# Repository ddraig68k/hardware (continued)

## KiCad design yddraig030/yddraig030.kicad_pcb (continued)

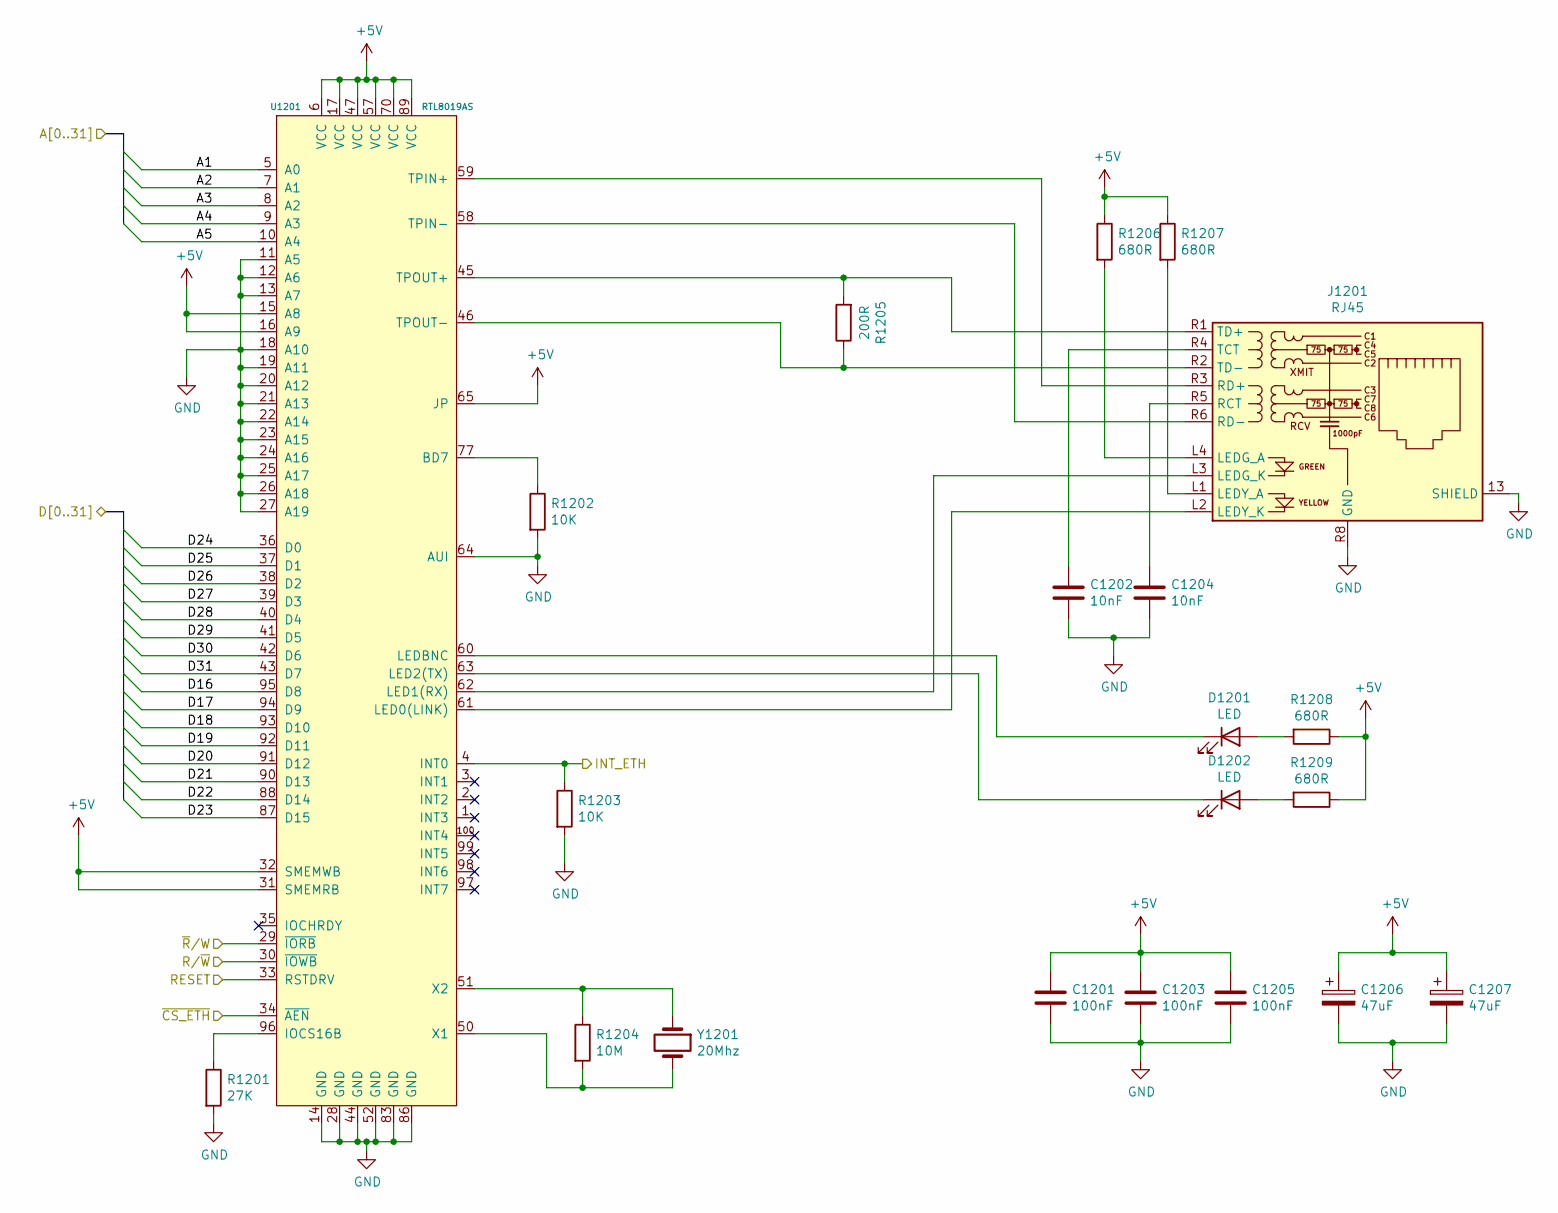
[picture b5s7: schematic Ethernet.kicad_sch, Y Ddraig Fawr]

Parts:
C1201, C1203, C1205: 100nF; C_0805_2012Metric
C1202, C1204: 10nF; C_0805_2012Metric
C1206, C1207: 47uF; CP_Elec_4x5.7
D1201, D1202: LED; LED_1206_3216Metric
J1201: RJ45; RJ45_Amphenol_RJMG1BD3B8K1ANR
R1201: 27K; R_0805_2012Metric
R1202, R1203: 10K; R_0805_2012Metric
R1204: 10M; R_0805_2012Metric
R1205: 200R; R_0805_2012Metric
R1206, R1207, R1208, R1209: 680R; R_0805_2012Metric
U1201: RTL8019AS
Y1201: 20Mhz; Crystal_SMD_HC49-SD

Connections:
+5V: C1201.1, C1203.1, C1205.1, C1206.1, C1207.1, R1206.1, R1207.1, R1208.1, R1209.1, U1201.6 (VCC), U1201.15 (A8), U1201.16 (A9), U1201.17 (VCC), U1201.31 (SMEMRB), U1201.32 (SMEMWB), U1201.47 (VCC), U1201.57 (VCC), U1201.65 (JP), U1201.70 (VCC), U1201.89 (VCC); also elsewhere on the board
/CPU and FPU/R/~W: U1201.30 (~IOWB); also elsewhere on the board
/Decode and Logic/INT_ETH: R1203.1, U1201.4 (INT0); also elsewhere on the board
/Decode and Logic/RESET: U1201.33 (RSTDRV); also elsewhere on the board
/Decode and Logic/~CS_ETH: U1201.34 (~AEN); also elsewhere on the board
/Decode and Logic/~R/W: U1201.29 (~IORB); also elsewhere on the board
/Ethernet/D16: U1201.95 (D8)
/Ethernet/D17: U1201.94 (D9)
/Ethernet/D18: U1201.93 (D10)
/Ethernet/D19: U1201.92 (D11)
/Ethernet/D20: U1201.91 (D12)
/Ethernet/D21: U1201.90 (D13)
/Ethernet/D22: U1201.88 (D14)
/Ethernet/D23: U1201.87 (D15)
/Ethernet/D24: U1201.36 (D0)
/Ethernet/D25: U1201.37 (D1)
/Ethernet/D26: U1201.38 (D2)
/Ethernet/D27: U1201.39 (D3)
/Ethernet/D28: U1201.40 (D4)
/Ethernet/D29: U1201.41 (D5)
/Ethernet/D30: U1201.42 (D6)
/Ethernet/D31: U1201.43 (D7)
/ROM and SRAM/A1: U1201.5 (A0); also elsewhere on the board
/ROM and SRAM/A2: U1201.7 (A1); also elsewhere on the board
/ROM and SRAM/A3: U1201.8 (A2); also elsewhere on the board
/ROM and SRAM/A4: U1201.9 (A3); also elsewhere on the board
/ROM and SRAM/A5: U1201.10 (A4); also elsewhere on the board
unnamed: C1202.1, J1201.R4 (TCT)
unnamed: C1204.1, J1201.R5 (RCT)
unnamed: D1201.1 (K), U1201.60 (LEDBNC)
unnamed: D1201.2 (A), R1208.2
unnamed: D1202.1 (K), U1201.63 (LED2(TX))
unnamed: D1202.2 (A), R1209.2
unnamed: J1201.L1 (LEDY_A), R1207.2
unnamed: J1201.L2 (LEDY_K), U1201.61 (LED0(LINK))
unnamed: J1201.L3 (LEDG_K), U1201.62 (LED1(RX))
unnamed: J1201.L4 (LEDG_A), R1206.2
unnamed: J1201.R1 (TD+), R1205.2, U1201.45 (TPOUT+)
unnamed: J1201.R2 (TD-), R1205.1, U1201.46 (TPOUT-)
unnamed: J1201.R3 (RD+), U1201.59 (TPIN+)
unnamed: J1201.R6 (RD-), U1201.58 (TPIN-)
unnamed: R1201.1, U1201.96 (IOCS16B)
unnamed: R1202.1, U1201.77 (BD7)
unnamed: R1204.1, U1201.51 (X2), Y1201.1
unnamed: R1204.2, U1201.50 (X1), Y1201.2

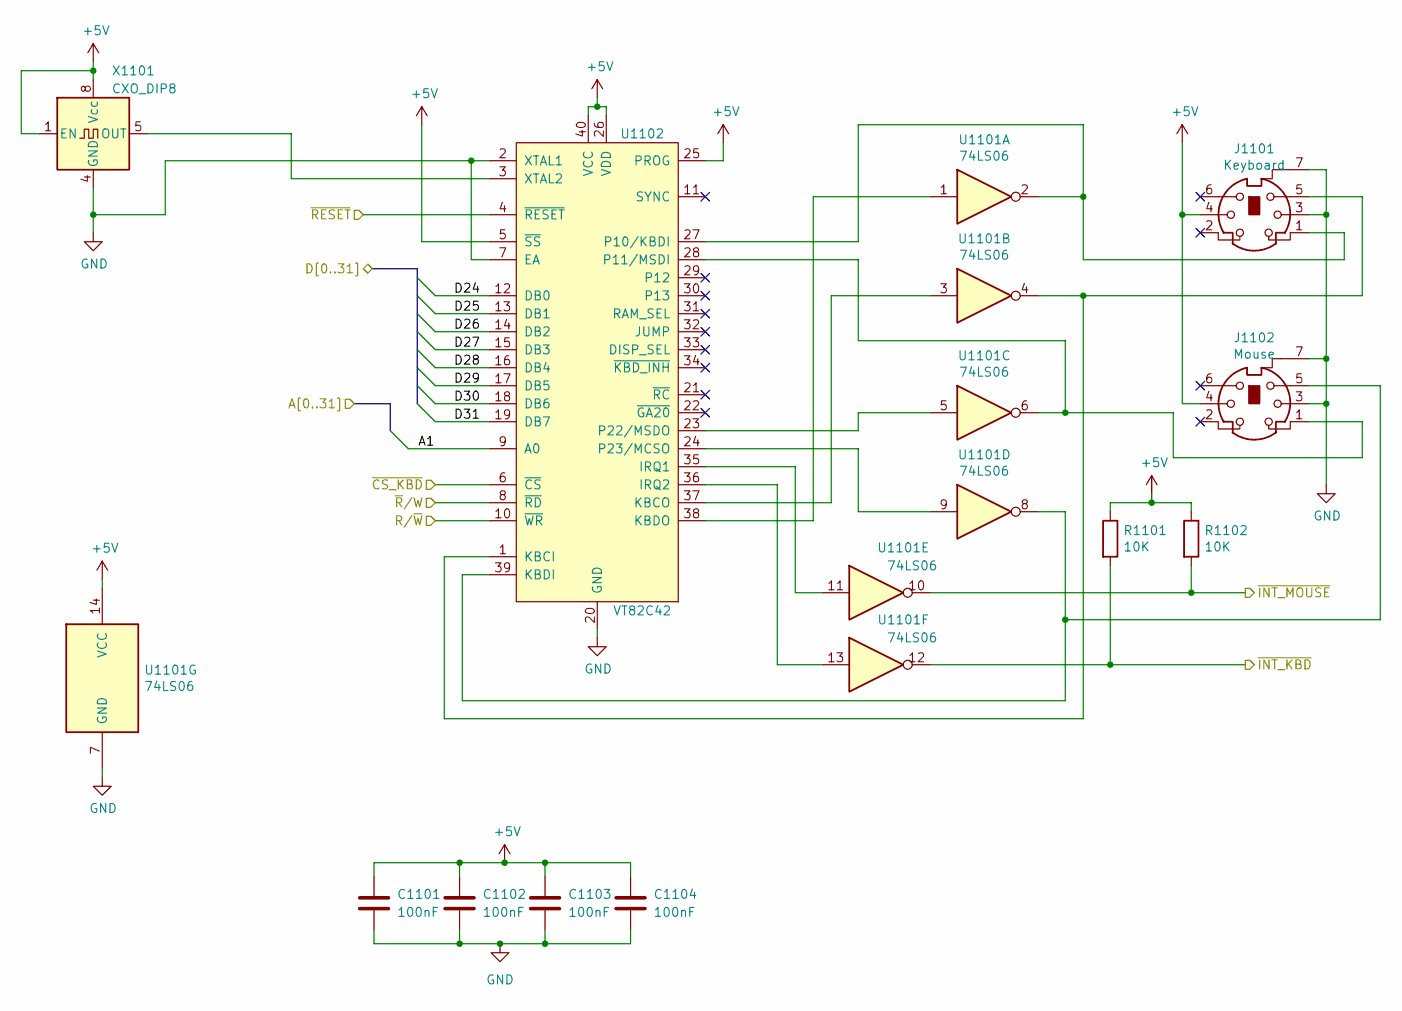
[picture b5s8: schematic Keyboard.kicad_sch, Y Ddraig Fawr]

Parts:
C1101, C1102, C1103, C1104: 100nF; C_Disc_D3.8mm_W2.6mm_P2.50mm
J1101: Keyboard; MINI-DIN-6-FULL-SHIELD
J1102: Mouse; MINI-DIN-6-FULL-SHIELD
R1101, R1102: 10K; R_Axial_DIN0207_L6.3mm_D2.5mm_P10.16mm_Horizontal
U1101: 74LS06; DIP-14_W7.62mm_Socket
U1102: VT82C42; DIP-40_W15.24mm_Socket
X1101: CXO_DIP8; Oscillator_DIP-8

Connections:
+5V: C1101.1, C1102.1, C1103.1, C1104.1, J1101.4, J1102.4, R1101.1, R1102.1, U1101.14 (VCC), U1102.5 (~SS), U1102.25 (PROG), U1102.26 (VDD), U1102.40 (VCC), X1101.1 (EN), X1101.8 (Vcc); also elsewhere on the board
/CPU and FPU/R/~W: U1102.10 (~WR); also elsewhere on the board
/CPU and FPU/~RESET: U1102.4 (~RESET); also elsewhere on the board
/Decode and Logic/~CS_KBD: U1102.6 (~CS); also elsewhere on the board
/Decode and Logic/~R/W: U1102.8 (~RD); also elsewhere on the board
/Interrupts/~INT_KBD: R1101.2, U1101.12; also elsewhere on the board
/Interrupts/~INT_MOUSE: R1102.2, U1101.10; also elsewhere on the board
/ROM and SRAM/A1: U1102.9 (A0); also elsewhere on the board
/ROM and SRAM/D24: U1102.12 (DB0); also elsewhere on the board
/ROM and SRAM/D25: U1102.13 (DB1); also elsewhere on the board
/ROM and SRAM/D26: U1102.14 (DB2); also elsewhere on the board
/ROM and SRAM/D27: U1102.15 (DB3); also elsewhere on the board
/ROM and SRAM/D28: U1102.16 (DB4); also elsewhere on the board
/ROM and SRAM/D29: U1102.17 (DB5); also elsewhere on the board
/ROM and SRAM/D30: U1102.18 (DB6); also elsewhere on the board
/ROM and SRAM/D31: U1102.19 (DB7); also elsewhere on the board
unnamed: J1101.1, U1101.2, U1102.27 (P10/KBDI)
unnamed: J1101.5, U1101.4, U1102.1 (KBCI)
unnamed: J1102.1, U1101.6, U1102.28 (P11/MSDI)
unnamed: J1102.5, U1101.8, U1102.39 (KBDI)
unnamed: U1101.1, U1102.38 (KBDO)
unnamed: U1101.3, U1102.37 (KBCO)
unnamed: U1101.5, U1102.23 (P22/MSDO)
unnamed: U1101.9, U1102.24 (P23/MCSO)
unnamed: U1101.11, U1102.35 (IRQ1)
unnamed: U1101.13, U1102.36 (IRQ2)
unnamed: U1102.3 (XTAL2), X1101.5 (OUT)

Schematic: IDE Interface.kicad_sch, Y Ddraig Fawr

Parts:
C601, C602, C603, C604: 100nF; C_0805_2012Metric
D601: Blue; LED_1206_3216Metric
J601: IDE LED; PinHeader_1x02_P2.54mm_Vertical
J602: IDE 5V; PinHeader_1x02_P2.54mm_Vertical
J603: IDE_Interface; IDC-Header_2x20_P2.54mm_Vertical
Q601: 2N7000; TO-92_Inline
R601, R602: 330R; R_0805_2012Metric
R603: 1M; R_0805_2012Metric
R604, R605: 10K; R_0805_2012Metric
RN601, RN602: 22R; R_Array_SIP8
U601: 74LS139; SO-16_3.9x9.9mm_P1.27mm

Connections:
+5V: C601.1, C602.1, C603.1, C604.1, D601.2 (A), J601.2, J602.2, R603.1, R605.2, U601.13 (A1), U601.14 (A0), U601.15 (E), U601.16 (VCC); also elsewhere on the board
/CPU and FPU/R/~W: RN602.1 (R1.1); also elsewhere on the board
/CPU and FPU/~RESET: RN602.5 (R3.1); also elsewhere on the board
/Decode and Logic/~CS_IDE: U601.1 (E); also elsewhere on the board
/Decode and Logic/~R/W: RN602.3 (R2.1); also elsewhere on the board
/IDE/ACTIVE: J603.39 (~ACTIVE), R601.2, R602.2
/IDE/~INT_IDE: Q601.3 (D), R603.2; also elsewhere on the board
/ROM and SRAM/A1: RN601.1 (R1.1); also elsewhere on the board
/ROM and SRAM/A2: RN601.3 (R2.1); also elsewhere on the board
/ROM and SRAM/A3: RN601.5 (R3.1); also elsewhere on the board
/ROM and SRAM/A7: U601.2 (A0); also elsewhere on the board
/ROM and SRAM/D16: J603.4 (D8); also elsewhere on the board
/ROM and SRAM/D17: J603.6 (D9); also elsewhere on the board
/ROM and SRAM/D18: J603.8 (D10); also elsewhere on the board
/ROM and SRAM/D19: J603.10 (D11); also elsewhere on the board
/ROM and SRAM/D20: J603.12 (D12); also elsewhere on the board
/ROM and SRAM/D21: J603.14 (D13); also elsewhere on the board
/ROM and SRAM/D22: J603.16 (D14); also elsewhere on the board
/ROM and SRAM/D23: J603.18 (D15); also elsewhere on the board
/ROM and SRAM/D24: J603.17 (D0); also elsewhere on the board
/ROM and SRAM/D25: J603.15 (D1); also elsewhere on the board
/ROM and SRAM/D26: J603.13 (D2); also elsewhere on the board
/ROM and SRAM/D27: J603.11 (D3); also elsewhere on the board
/ROM and SRAM/D28: J603.9 (D4); also elsewhere on the board
/ROM and SRAM/D29: J603.7 (D5); also elsewhere on the board
/ROM and SRAM/D30: J603.5 (D6); also elsewhere on the board
/ROM and SRAM/D31: J603.3 (D7); also elsewhere on the board
unnamed: D601.1 (K), R602.1
unnamed: J601.1, R601.1
unnamed: J602.1, J603.20 (KEY)
unnamed: J603.1 (~RESET), RN602.6 (R3.2)
unnamed: J603.21 (DMARQ), R604.1
unnamed: J603.23 (~DIOW), RN602.2 (R1.2)
unnamed: J603.25 (~DIOR), RN602.4 (R2.2)
unnamed: J603.29 (~DMACK), R605.1
unnamed: J603.33 (A1), RN601.4 (R2.2)
unnamed: J603.35 (A0), RN601.2 (R1.2)
unnamed: J603.36 (A2), RN601.6 (R3.2)
unnamed: J603.37 (~IDE_CS0), U601.4 (O0)
unnamed: J603.38 (~IDE_CS1), U601.5 (O1)

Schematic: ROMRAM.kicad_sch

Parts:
C401, C402, C403, C404, C405: 100nF; C_0805_2012Metric
U401, U403: SST39SF040; DIP-32_W15.24mm_Socket
U402, U404: AS6C4008-55PCN; DIP-32_W15.24mm
U405: 74LS32; SO-14_3.9x8.65mm_P1.27mm

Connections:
+5V: C401.1, C402.1, C403.1, C404.1, C405.1, U401.32 (VCC), U402.32 (VCC), U403.32 (VCC), U404.32 (VCC), U405.14 (VCC); also elsewhere on the board
/CPU and FPU/R/~W: U401.31 (PGM), U402.29 (WE#), U403.31 (PGM), U404.29 (WE#); also elsewhere on the board
/Decode and Logic/~CS_ROM: U405.2, U405.10; also elsewhere on the board
/Decode and Logic/~CS_SRAM: U405.5, U405.13; also elsewhere on the board
/Decode and Logic/~LDS: U405.9, U405.12; also elsewhere on the board
/Decode and Logic/~R/W: U401.24 (OE), U402.24 (OE#), U403.24 (OE), U404.24 (OE#); also elsewhere on the board
/Decode and Logic/~UDS: U405.1, U405.4; also elsewhere on the board
/ROM and SRAM/A1: U401.12 (A0), U402.12 (A0), U403.12 (A0), U404.12 (A0); also elsewhere on the board
/ROM and SRAM/A2: U401.11 (A1), U402.11 (A1), U403.11 (A1), U404.11 (A1); also elsewhere on the board
/ROM and SRAM/A3: U401.10 (A2), U402.10 (A2), U403.10 (A2), U404.10 (A2); also elsewhere on the board
/ROM and SRAM/A4: U401.9 (A3), U402.9 (A3), U403.9 (A3), U404.9 (A3); also elsewhere on the board
/ROM and SRAM/A5: U401.8 (A4), U402.8 (A4), U403.8 (A4), U404.8 (A4); also elsewhere on the board
/ROM and SRAM/A6: U401.7 (A5), U402.7 (A5), U403.7 (A5), U404.7 (A5); also elsewhere on the board
/ROM and SRAM/A7: U401.6 (A6), U402.6 (A6), U403.6 (A6), U404.6 (A6); also elsewhere on the board
/ROM and SRAM/A8: U401.5 (A7), U402.5 (A7), U403.5 (A7), U404.5 (A7); also elsewhere on the board
/ROM and SRAM/A9: U401.27 (A8), U402.27 (A8), U403.27 (A8), U404.27 (A8); also elsewhere on the board
/ROM and SRAM/A10: U401.26 (A9), U402.26 (A9), U403.26 (A9), U404.26 (A9); also elsewhere on the board
/ROM and SRAM/A11: U401.23 (A10), U402.23 (A10), U403.23 (A10), U404.23 (A10); also elsewhere on the board
/ROM and SRAM/A12: U401.25 (A11), U402.25 (A11), U403.25 (A11), U404.25 (A11); also elsewhere on the board
/ROM and SRAM/A13: U401.4 (A12), U402.4 (A12), U403.4 (A12), U404.4 (A12); also elsewhere on the board
/ROM and SRAM/A14: U401.28 (A13), U402.28 (A13), U403.28 (A13), U404.28 (A13); also elsewhere on the board
/ROM and SRAM/A15: U401.29 (A14), U402.3 (A14), U403.29 (A14), U404.3 (A14); also elsewhere on the board
/ROM and SRAM/A16: U401.3 (A15), U402.31 (A15), U403.3 (A15), U404.31 (A15); also elsewhere on the board
/ROM and SRAM/A17: U401.2 (A16), U402.2 (A16), U403.2 (A16), U404.2 (A16); also elsewhere on the board
/ROM and SRAM/A18: U401.30 (A17), U402.30 (A17), U403.30 (A17), U404.30 (A17); also elsewhere on the board
/ROM and SRAM/A19: U401.1 (A18), U402.1 (A18), U403.1 (A18), U404.1 (A18); also elsewhere on the board
/ROM and SRAM/D16: U401.13 (D0), U402.13 (DQ0); also elsewhere on the board
/ROM and SRAM/D17: U401.14 (D1), U402.14 (DQ1); also elsewhere on the board
/ROM and SRAM/D18: U401.15 (D2), U402.15 (DQ2); also elsewhere on the board
/ROM and SRAM/D19: U401.17 (D3), U402.17 (DQ3); also elsewhere on the board
/ROM and SRAM/D20: U401.18 (D4), U402.18 (DQ4); also elsewhere on the board
/ROM and SRAM/D21: U401.19 (D5), U402.19 (DQ5); also elsewhere on the board
/ROM and SRAM/D22: U401.20 (D6), U402.20 (DQ6); also elsewhere on the board
/ROM and SRAM/D23: U401.21 (D7), U402.21 (DQ7); also elsewhere on the board
/ROM and SRAM/D24: U403.13 (D0), U404.13 (DQ0); also elsewhere on the board
/ROM and SRAM/D25: U403.14 (D1), U404.14 (DQ1); also elsewhere on the board
/ROM and SRAM/D26: U403.15 (D2), U404.15 (DQ2); also elsewhere on the board
/ROM and SRAM/D27: U403.17 (D3), U404.17 (DQ3); also elsewhere on the board
/ROM and SRAM/D28: U403.18 (D4), U404.18 (DQ4); also elsewhere on the board
/ROM and SRAM/D29: U403.19 (D5), U404.19 (DQ5); also elsewhere on the board
/ROM and SRAM/D30: U403.20 (D6), U404.20 (DQ6); also elsewhere on the board
/ROM and SRAM/D31: U403.21 (D7), U404.21 (DQ7); also elsewhere on the board
unnamed: U401.22 (CE), U405.8
unnamed: U402.22 (CE#), U405.11
unnamed: U403.22 (CE), U405.3
unnamed: U404.22 (CE#), U405.6

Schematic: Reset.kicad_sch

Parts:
C201, C203: 10uF; CP_Elec_4x5.3
C202: 10nF; C_0805_2012Metric
D201: RED; LED_1206_3216Metric
D202: GREEN; LED_1206_3216Metric
J201: ExtReset; PinHeader_1x02_P2.54mm_Vertical
J202: Ext RUN LED; PinHeader_1x02_P2.54mm_Vertical
Q201, Q202: BC858; SOT-23
R201, R205: 1K; R_0805_2012Metric
R202, R206, R207: 150R; R_0805_2012Metric
R203: 10K; R_0805_2012Metric
R204: 38K; R_0805_2012Metric
SW201: Reset; SW_PUSH_6mm_H4.3mm
U201: NE555P; SO-8_5.3x6.2mm_P1.27mm

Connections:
+5V: Q201.2 (E), Q202.2 (E), R203.1, R204.1, U201.4 (R), U201.8 (VCC); also elsewhere on the board
/CPU and FPU/~RESET: R201.2; also elsewhere on the board
/Decode and Logic/RESET: U201.3 (Q); also elsewhere on the board
/Decode and Logic/RUN: R205.2; also elsewhere on the board
unnamed: C201.1, J201.1, R203.2, SW201.2 (B), U201.2 (TR)
unnamed: C202.1, U201.5 (CV)
unnamed: C203.1, R204.2, U201.6 (THR), U201.7 (DIS)
unnamed: D201.1 (K), R202.2
unnamed: D201.2 (A), Q201.3 (C)
unnamed: D202.1 (K), R206.2
unnamed: D202.2 (A), J202.1, Q202.3 (C)
unnamed: J202.2, R207.2
unnamed: Q201.1 (B), R201.1
unnamed: Q202.1 (B), R205.1

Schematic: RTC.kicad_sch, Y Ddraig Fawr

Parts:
BT1301: CR2032; BatteryHolder_Keystone_103_1x20mm
C1301, C1302: 100nF; C_0805_2012Metric
C1303: 10uF; CP_Elec_4x5.3
D1301: 1N4148; D_SOD-123
Q1301: BC549B; TO-92
Q1302: 2N4403; TO-92
R1301, R1302, R1303: 4K7; R_0805_2012Metric
U1301: RTC-72421; DIP-18_W7.62mm_Socket

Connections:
+5V: C1301.1, C1302.1, Q1302.1 (E), R1301.1; also elsewhere on the board
/CPU and FPU/R/~W: U1301.10 (~WR); also elsewhere on the board
/CPU and FPU/~RESET: U1301.15 (CS1); also elsewhere on the board
/Decode and Logic/~CS_RTC: U1301.2 (~CS0); also elsewhere on the board
/Decode and Logic/~R/W: U1301.8 (~RD); also elsewhere on the board
/ROM and SRAM/A1: U1301.4 (A0); also elsewhere on the board
/ROM and SRAM/A2: U1301.5 (A1); also elsewhere on the board
/ROM and SRAM/A3: U1301.6 (A2); also elsewhere on the board
/ROM and SRAM/A4: U1301.7 (A3); also elsewhere on the board
/ROM and SRAM/D24: U1301.14 (D0); also elsewhere on the board
/ROM and SRAM/D25: U1301.13 (D1); also elsewhere on the board
/ROM and SRAM/D26: U1301.12 (D2); also elsewhere on the board
/ROM and SRAM/D27: U1301.11 (D3); also elsewhere on the board
unnamed: BT1301.1 (+), D1301.2 (A)
unnamed: C1303.1, D1301.1 (K), Q1302.3 (C), U1301.3 (ALE), U1301.18 (VDD)
unnamed: Q1301.2 (B), R1301.2, R1302.1
unnamed: Q1301.3 (C), R1303.2
unnamed: Q1302.2 (B), R1303.1

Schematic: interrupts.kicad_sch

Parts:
C1501, C1502, C1503: 100nF; C_0805_2012Metric
RN1501, RN1502: 10K; R_Array_SIP9
U1501: 74LS541; SO-20_5.3x12.6mm_P1.27mm
U1502: 74LS21; SO-14_3.9x8.65mm_P1.27mm
U1503: 74LS148; SO-16_3.9x9.9mm_P1.27mm

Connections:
+5V: C1501.1, C1502.1, C1503.1, RN1501.1 (common), RN1502.1 (common), U1501.20 (VCC), U1502.14 (VCC), U1503.16 (VCC); also elsewhere on the board
/CPU and FPU/~IPL0: U1503.9 (S0); also elsewhere on the board
/CPU and FPU/~IPL1: U1503.7 (S1); also elsewhere on the board
/CPU and FPU/~IPL2: U1503.6 (S2); also elsewhere on the board
/Decode and Logic/~CS_INTERRUPT: U1501.1 (G1); also elsewhere on the board
/Decode and Logic/~INT_ETH: RN1502.6 (R5), U1503.3 (I6); also elsewhere on the board
/Expansion Slots/~EXT_IRQ1: RN1502.3 (R2), U1503.11 (I1); also elsewhere on the board
/Expansion Slots/~EXT_IRQ2: RN1501.8 (R7), U1501.3 (A1), U1502.2; also elsewhere on the board
/Expansion Slots/~EXT_IRQ3: RN1501.7 (R6), U1501.4 (A2), U1502.4; also elsewhere on the board
/Expansion Slots/~EXT_IRQ4: RN1501.6 (R5), U1501.5 (A3), U1502.5; also elsewhere on the board
/IDE/~INT_IDE: RN1502.4 (R3), U1503.12 (I2); also elsewhere on the board
/Interrupts/~INT_DUART: U1503.1 (I4); also elsewhere on the board
/Interrupts/~INT_KBD: U1503.13 (I3); also elsewhere on the board
/Interrupts/~INT_MOUSE: RN1502.5 (R4), U1503.2 (I5); also elsewhere on the board
/ROM and SRAM/D24: U1501.18 (Y0); also elsewhere on the board
/ROM and SRAM/D25: U1501.17 (Y1); also elsewhere on the board
/ROM and SRAM/D26: U1501.16 (Y2); also elsewhere on the board
/ROM and SRAM/D27: U1501.15 (Y3); also elsewhere on the board
/ROM and SRAM/D28: U1501.14 (Y4); also elsewhere on the board
/ROM and SRAM/D29: U1501.13 (Y5); also elsewhere on the board
/ROM and SRAM/D30: U1501.12 (Y6); also elsewhere on the board
/ROM and SRAM/D31: U1501.11 (Y7); also elsewhere on the board
unnamed: RN1501.2 (R1), U1501.9 (A7)
unnamed: RN1501.3 (R2), U1501.8 (A6)
unnamed: RN1501.4 (R3), U1501.7 (A5)
unnamed: RN1501.5 (R4), U1501.6 (A4)
unnamed: RN1501.9 (R8), U1501.2 (A0), U1502.1
unnamed: RN1502.2 (R1), U1503.10 (IO)
unnamed: U1502.6, U1503.4 (I7)

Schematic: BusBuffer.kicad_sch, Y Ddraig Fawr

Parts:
C901, C902, C903, C904, C905, C906, C907, C908, C909, C910: 100nF; C_0805_2012Metric
RN901, RN902, RN903, RN904: 10K; R_Array_SIP9
U901, U902, U903, U904, U905, U906, U907, U908, U909: 74LS245; SO-20_5.3x12.6mm_P1.27mm

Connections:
+5V: C901.1, C902.1, C903.1, C904.1, C905.1, C906.1, C907.1, C908.1, C909.1, C910.1, U901.1 (A->B), U901.20 (VCC), U902.1 (A->B), U902.20 (VCC), U903.1 (A->B), U903.20 (VCC), U904.1 (A->B), U904.20 (VCC), U905.20 (VCC), U906.20 (VCC), U907.20 (VCC), U908.20 (VCC), U909.20 (VCC); also elsewhere on the board
/CPU and FPU/CPU_CLK: U904.9 (A7); also elsewhere on the board
/CPU and FPU/R/~W: U905.15 (B3); also elsewhere on the board
/CPU and FPU/SIZ0: U904.6 (A4); also elsewhere on the board
/CPU and FPU/SIZ1: U904.7 (A5); also elsewhere on the board
/CPU and FPU/~AS: U901.19 (CE), U902.19 (CE), U903.19 (CE), U904.19 (CE), U905.14 (B4); also elsewhere on the board
/CPU and FPU/~DS: U904.5 (A3); also elsewhere on the board
/CPU and FPU/~RESET: U905.18 (B0); also elsewhere on the board
/Decode and Logic/CLK10: U905.11 (B7); also elsewhere on the board
/Decode and Logic/~EXT_DBEN: U906.19 (CE), U907.19 (CE), U908.19 (CE), U909.19 (CE); also elsewhere on the board
/Decode and Logic/~LDS: U905.17 (B1); also elsewhere on the board
/Decode and Logic/~R/W: U906.1 (A->B), U907.1 (A->B), U908.1 (A->B), U909.1 (A->B); also elsewhere on the board
/Decode and Logic/~UDS: U905.16 (B2); also elsewhere on the board
/Decode and Logic/~VMA: U905.13 (B5); also elsewhere on the board
/Expansion Slots/BA0: U901.18 (B0); also elsewhere on the board
/Expansion Slots/BA1: U901.17 (B1); also elsewhere on the board
/Expansion Slots/BA2: U901.16 (B2); also elsewhere on the board
/Expansion Slots/BA3: U901.15 (B3); also elsewhere on the board
/Expansion Slots/BA4: U901.14 (B4); also elsewhere on the board
/Expansion Slots/BA5: U901.13 (B5); also elsewhere on the board
/Expansion Slots/BA6: U901.12 (B6); also elsewhere on the board
/Expansion Slots/BA7: U901.11 (B7); also elsewhere on the board
/Expansion Slots/BA8: U902.18 (B0); also elsewhere on the board
/Expansion Slots/BA9: U902.17 (B1); also elsewhere on the board
/Expansion Slots/BA10: U902.16 (B2); also elsewhere on the board
/Expansion Slots/BA11: U902.15 (B3); also elsewhere on the board
/Expansion Slots/BA12: U902.14 (B4); also elsewhere on the board
/Expansion Slots/BA13: U902.13 (B5); also elsewhere on the board
/Expansion Slots/BA14: U902.12 (B6); also elsewhere on the board
/Expansion Slots/BA15: U902.11 (B7); also elsewhere on the board
/Expansion Slots/BA16: U903.18 (B0); also elsewhere on the board
/Expansion Slots/BA17: U903.17 (B1); also elsewhere on the board
/Expansion Slots/BA18: U903.16 (B2); also elsewhere on the board
/Expansion Slots/BA19: U903.15 (B3); also elsewhere on the board
/Expansion Slots/BA20: U903.14 (B4); also elsewhere on the board
/Expansion Slots/BA21: U903.13 (B5); also elsewhere on the board
/Expansion Slots/BA22: U903.12 (B6); also elsewhere on the board
/Expansion Slots/BA23: U903.11 (B7); also elsewhere on the board
/Expansion Slots/BA24: U904.18 (B0); also elsewhere on the board
/Expansion Slots/BA25: U904.17 (B1); also elsewhere on the board
/Expansion Slots/BA26: U904.16 (B2); also elsewhere on the board
/Expansion Slots/BCLK10: U905.9 (A7); also elsewhere on the board
/Expansion Slots/BCPUCLK: U904.11 (B7); also elsewhere on the board
/Expansion Slots/BD0: RN901.2 (R1), U906.12 (B6); also elsewhere on the board
/Expansion Slots/BD1: RN901.3 (R2), U906.11 (B7); also elsewhere on the board
/Expansion Slots/BD2: RN901.4 (R3), U906.14 (B4); also elsewhere on the board
/Expansion Slots/BD3: RN901.5 (R4), U906.13 (B5); also elsewhere on the board
/Expansion Slots/BD4: RN901.6 (R5), U906.16 (B2); also elsewhere on the board
/Expansion Slots/BD5: RN901.7 (R6), U906.15 (B3); also elsewhere on the board
/Expansion Slots/BD6: RN901.8 (R7), U906.18 (B0); also elsewhere on the board
/Expansion Slots/BD7: RN901.9 (R8), U906.17 (B1); also elsewhere on the board
/Expansion Slots/BD8: RN902.2 (R1), U907.12 (B6); also elsewhere on the board
/Expansion Slots/BD9: RN902.3 (R2), U907.11 (B7); also elsewhere on the board
/Expansion Slots/BD10: RN902.4 (R3), U907.14 (B4); also elsewhere on the board
/Expansion Slots/BD11: RN902.5 (R4), U907.13 (B5); also elsewhere on the board
/Expansion Slots/BD12: RN902.6 (R5), U907.16 (B2); also elsewhere on the board
/Expansion Slots/BD13: RN902.7 (R6), U907.15 (B3); also elsewhere on the board
/Expansion Slots/BD14: RN902.8 (R7), U907.18 (B0); also elsewhere on the board
/Expansion Slots/BD15: RN902.9 (R8), U907.17 (B1); also elsewhere on the board
/Expansion Slots/BD16: RN903.2 (R1), U908.11 (B7); also elsewhere on the board
/Expansion Slots/BD17: RN903.3 (R2), U908.12 (B6); also elsewhere on the board
/Expansion Slots/BD18: RN903.4 (R3), U908.13 (B5); also elsewhere on the board
/Expansion Slots/BD19: RN903.5 (R4), U908.14 (B4); also elsewhere on the board
/Expansion Slots/BD20: RN903.6 (R5), U908.15 (B3); also elsewhere on the board
/Expansion Slots/BD21: RN903.7 (R6), U908.16 (B2); also elsewhere on the board
/Expansion Slots/BD22: RN903.8 (R7), U908.17 (B1); also elsewhere on the board
/Expansion Slots/BD23: RN903.9 (R8), U908.18 (B0); also elsewhere on the board
/Expansion Slots/BD24: RN904.2 (R1), U909.11 (B7); also elsewhere on the board
/Expansion Slots/BD25: RN904.3 (R2), U909.12 (B6); also elsewhere on the board
/Expansion Slots/BD26: RN904.4 (R3), U909.13 (B5); also elsewhere on the board
/Expansion Slots/BD27: RN904.5 (R4), U909.14 (B4); also elsewhere on the board
/Expansion Slots/BD28: RN904.6 (R5), U909.15 (B3); also elsewhere on the board
/Expansion Slots/BD29: RN904.7 (R6), U909.16 (B2); also elsewhere on the board
/Expansion Slots/BD30: RN904.8 (R7), U909.17 (B1); also elsewhere on the board
/Expansion Slots/BD31: RN904.9 (R8), U909.18 (B0); also elsewhere on the board
/Expansion Slots/BRD/~WR: U905.5 (A3); also elsewhere on the board
/Expansion Slots/BSIZ0: U904.14 (B4); also elsewhere on the board
/Expansion Slots/BSIZ1: U904.13 (B5); also elsewhere on the board
/Expansion Slots/~BAS: U905.6 (A4); also elsewhere on the board
/Expansion Slots/~BDS: U904.15 (B3); also elsewhere on the board
/Expansion Slots/~BLDS: U905.3 (A1); also elsewhere on the board
/Expansion Slots/~BRESET: U905.2 (A0); also elsewhere on the board
/Expansion Slots/~BUDS: U905.4 (A2); also elsewhere on the board
/Expansion Slots/~BVMA: U905.7 (A5); also elsewhere on the board
/ROM and SRAM/A0: U901.2 (A0); also elsewhere on the board
/ROM and SRAM/A1: U901.3 (A1); also elsewhere on the board
/ROM and SRAM/A2: U901.4 (A2); also elsewhere on the board
/ROM and SRAM/A3: U901.5 (A3); also elsewhere on the board
/ROM and SRAM/A4: U901.6 (A4); also elsewhere on the board
/ROM and SRAM/A5: U901.7 (A5); also elsewhere on the board
/ROM and SRAM/A6: U901.8 (A6); also elsewhere on the board
/ROM and SRAM/A7: U901.9 (A7); also elsewhere on the board
/ROM and SRAM/A8: U902.2 (A0); also elsewhere on the board
/ROM and SRAM/A9: U902.3 (A1); also elsewhere on the board
/ROM and SRAM/A10: U902.4 (A2); also elsewhere on the board
/ROM and SRAM/A11: U902.5 (A3); also elsewhere on the board
/ROM and SRAM/A12: U902.6 (A4); also elsewhere on the board
/ROM and SRAM/A13: U902.7 (A5); also elsewhere on the board
/ROM and SRAM/A14: U902.8 (A6); also elsewhere on the board
/ROM and SRAM/A15: U902.9 (A7); also elsewhere on the board
/ROM and SRAM/A16: U903.2 (A0); also elsewhere on the board
/ROM and SRAM/A17: U903.3 (A1); also elsewhere on the board
/ROM and SRAM/A18: U903.4 (A2); also elsewhere on the board
/ROM and SRAM/A19: U903.5 (A3); also elsewhere on the board
/ROM and SRAM/A20: U903.6 (A4); also elsewhere on the board
/ROM and SRAM/A21: U903.7 (A5); also elsewhere on the board
/ROM and SRAM/A22: U903.8 (A6); also elsewhere on the board
/ROM and SRAM/A23: U903.9 (A7); also elsewhere on the board
/ROM and SRAM/A24: U904.2 (A0); also elsewhere on the board
/ROM and SRAM/A25: U904.3 (A1); also elsewhere on the board
/ROM and SRAM/A26: U904.4 (A2); also elsewhere on the board
/ROM and SRAM/D0: U906.8 (A6); also elsewhere on the board
/ROM and SRAM/D1: U906.9 (A7); also elsewhere on the board
/ROM and SRAM/D2: U906.6 (A4); also elsewhere on the board
/ROM and SRAM/D3: U906.7 (A5); also elsewhere on the board
/ROM and SRAM/D4: U906.4 (A2); also elsewhere on the board
/ROM and SRAM/D5: U906.5 (A3); also elsewhere on the board
/ROM and SRAM/D6: U906.2 (A0); also elsewhere on the board
/ROM and SRAM/D7: U906.3 (A1); also elsewhere on the board
/ROM and SRAM/D8: U907.8 (A6); also elsewhere on the board
/ROM and SRAM/D9: U907.9 (A7); also elsewhere on the board
/ROM and SRAM/D10: U907.6 (A4); also elsewhere on the board
/ROM and SRAM/D11: U907.7 (A5); also elsewhere on the board
/ROM and SRAM/D12: U907.4 (A2); also elsewhere on the board
/ROM and SRAM/D13: U907.5 (A3); also elsewhere on the board
/ROM and SRAM/D14: U907.2 (A0); also elsewhere on the board
/ROM and SRAM/D15: U907.3 (A1); also elsewhere on the board
/ROM and SRAM/D16: U908.9 (A7); also elsewhere on the board
/ROM and SRAM/D17: U908.8 (A6); also elsewhere on the board
/ROM and SRAM/D18: U908.7 (A5); also elsewhere on the board
/ROM and SRAM/D19: U908.6 (A4); also elsewhere on the board
/ROM and SRAM/D20: U908.5 (A3); also elsewhere on the board
/ROM and SRAM/D21: U908.4 (A2); also elsewhere on the board
/ROM and SRAM/D22: U908.3 (A1); also elsewhere on the board
/ROM and SRAM/D23: U908.2 (A0); also elsewhere on the board
/ROM and SRAM/D24: U909.9 (A7); also elsewhere on the board
/ROM and SRAM/D25: U909.8 (A6); also elsewhere on the board
/ROM and SRAM/D26: U909.7 (A5); also elsewhere on the board
/ROM and SRAM/D27: U909.6 (A4); also elsewhere on the board
/ROM and SRAM/D28: U909.5 (A3); also elsewhere on the board
/ROM and SRAM/D29: U909.4 (A2); also elsewhere on the board
/ROM and SRAM/D30: U909.3 (A1); also elsewhere on the board
/ROM and SRAM/D31: U909.2 (A0); also elsewhere on the board

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
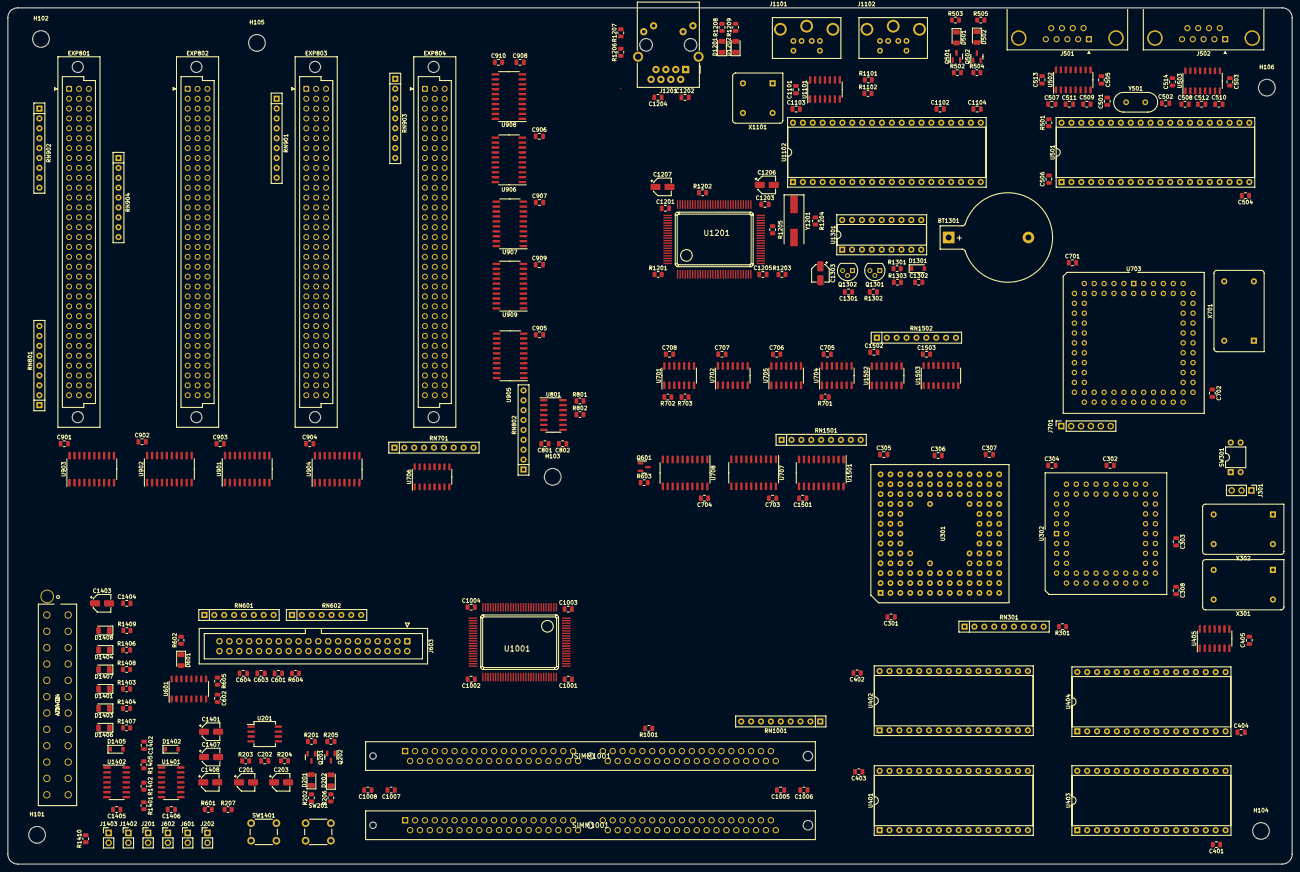
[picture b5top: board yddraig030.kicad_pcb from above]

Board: 4 copper layers, 330.0 x 220.0 mm, 248 parts (0 on the bottom side), 403 nets.

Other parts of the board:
C501: 10pF; C_0805_2012Metric
C502: 5pF; C_0805_2012Metric
C503, C504, C505, C506, C507, C508, C509, C510, C511, C512, C513, C514: 100nF; C_0805_2012Metric
D501, D502: Green; LED_1206_3216Metric
J501: Serial1; DSUB-9_Male_Horizontal_P2.77x2.84mm_EdgePinOffset4.94mm_Hou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
J502: Serial2; DSUB-9_Male_Horizontal_P2.77x2.84mm_EdgePinOffset4.94mm_Hou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
Q501, Q502: BC858; SOT-23
R501: 4K7; R_0805_2012Metric
R502, R503, R504, R505: 150R; R_0805_2012Metric
U501: 68681; DIP-40_W15.24mm_Socket
U502, U503: MAX202; SO-16_3.9x9.9mm_P1.27mm
Y501: 3.6864MHz; Crystal_HC18-U_Vertical

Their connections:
+5V: C503.1, C504.1, C505.1, C506.1, C513.1, C514.2, Q501.2 (E), Q502.2 (E), R501.1, U501.40 (VCC), U502.16 (VCC), U503.16 (VCC); also elsewhere on the board
/CPU and FPU/R/~W: U501.8 (R/W); also elsewhere on the board
/CPU and FPU/~RESET: U501.34 (RESET); also elsewhere on the board
/Decode and Logic/~CS_DUART: U501.35 (CS); also elsewhere on the board
/Decode and Logic/~DTACK_DUART: U501.9 (DTACK); also elsewhere on the board
/Interrupts/~INT_DUART: U501.21 (IRQ); also elsewhere on the board
/ROM and SRAM/A1: U501.1 (RS1); also elsewhere on the board
/ROM and SRAM/A2: U501.3 (RS2); also elsewhere on the board
/ROM and SRAM/A3: U501.5 (RS3); also elsewhere on the board
/ROM and SRAM/A4: U501.6 (RS4); also elsewhere on the board
/ROM and SRAM/D24: U501.25 (D0); also elsewhere on the board
/ROM and SRAM/D25: U501.16 (D1); also elsewhere on the board
/ROM and SRAM/D26: U501.24 (D2); also elsewhere on the board
/ROM and SRAM/D27: U501.17 (D3); also elsewhere on the board
/ROM and SRAM/D28: U501.23 (D4); also elsewhere on the board
/ROM and SRAM/D29: U501.18 (D5); also elsewhere on the board
/ROM and SRAM/D30: U501.22 (D6); also elsewhere on the board
/ROM and SRAM/D31: U501.19 (D7); also elsewhere on the board
/Serial/RXDA: R504.2, U501.31 (RXDA), U502.12 (R1OUT)
/Serial/TXDA: R502.2, U501.30 (TXDA), U502.11 (T1IN)
unnamed: C501.1, U501.33 (X2), Y501.1
unnamed: C502.1, U501.32 (X1/CLK), Y501.2
unnamed: C507.1, U502.1 (C1+)
unnamed: C507.2, U502.3 (C1-)
unnamed: C508.1, U503.1 (C1+)
unnamed: C508.2, U503.3 (C1-)
unnamed: C509.1, U502.6 (VS-)
unnamed: C510.1, U503.6 (VS-)
unnamed: C511.1, U502.4 (C2+)
unnamed: C511.2, U502.5 (C2-)
unnamed: C512.1, U503.4 (C2+)
unnamed: C512.2, U503.5 (C2-)
unnamed: C513.2, U502.2 (VS+)
unnamed: C514.1, U503.2 (VS+)
unnamed: D501.1 (K), R503.1
unnamed: D501.2 (A), Q501.3 (C)
unnamed: D502.1 (K), R505.1
unnamed: D502.2 (A), Q502.3 (C)
unnamed: J501.2, U502.13 (R1IN)
unnamed: J501.3, U502.14 (T1OUT)
unnamed: J501.7, U502.7 (T2OUT)
unnamed: J501.8, U502.8 (R2IN)
unnamed: J502.2, U503.13 (R1IN)
unnamed: J502.3, U503.14 (T1OUT)
unnamed: J502.7, U503.7 (T2OUT)
unnamed: J502.8, U503.8 (R2IN)
unnamed: Q501.1 (B), R502.1
unnamed: Q502.1 (B), R504.1
unnamed: R501.2, U501.37 (IACK)
unnamed: U501.4 (IP1), U503.9 (R2OUT)
unnamed: U501.7 (IP0), U502.9 (R2OUT)
unnamed: U501.10 (RXDB), U503.12 (R1OUT)
unnamed: U501.11 (TXDB), U503.11 (T1IN)
unnamed: U501.12 (OP1), U503.10 (T2IN)
unnamed: U501.29 (OP0), U502.10 (T2IN)
